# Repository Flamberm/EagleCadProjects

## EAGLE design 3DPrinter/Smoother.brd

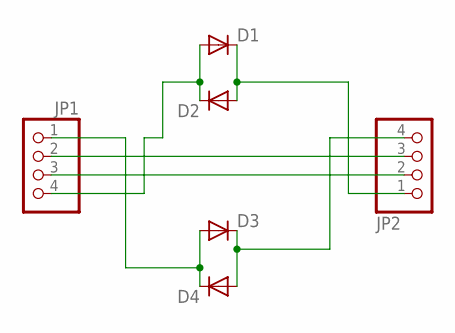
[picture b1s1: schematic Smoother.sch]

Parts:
D1, D2, D3, D4: DIODE_ES1J; DO214AC
JP1, JP2: PINHD-1X4/90; 1X04/90

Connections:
unnamed: D3.A, D4.C, JP1.1
unnamed: JP1.2, JP2.3
unnamed: JP1.3, JP2.2
unnamed: D1.C, D2.A, JP2.1
unnamed: D1.A, D2.C, JP1.4
unnamed: D3.C, D4.A, JP2.4

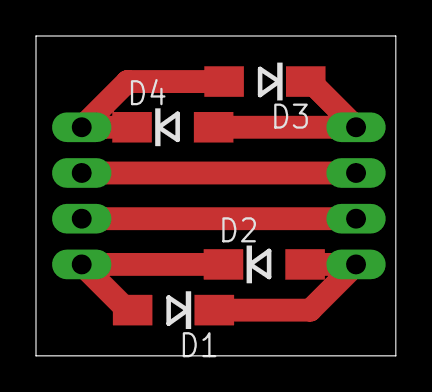
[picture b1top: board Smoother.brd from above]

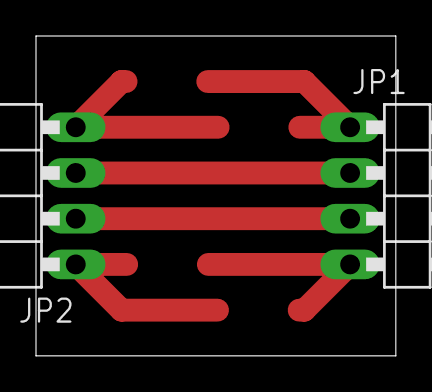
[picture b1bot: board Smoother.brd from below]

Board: 2 copper layers, 20.0 x 17.8 mm, 6 parts (2 on the bottom side), 6 nets.

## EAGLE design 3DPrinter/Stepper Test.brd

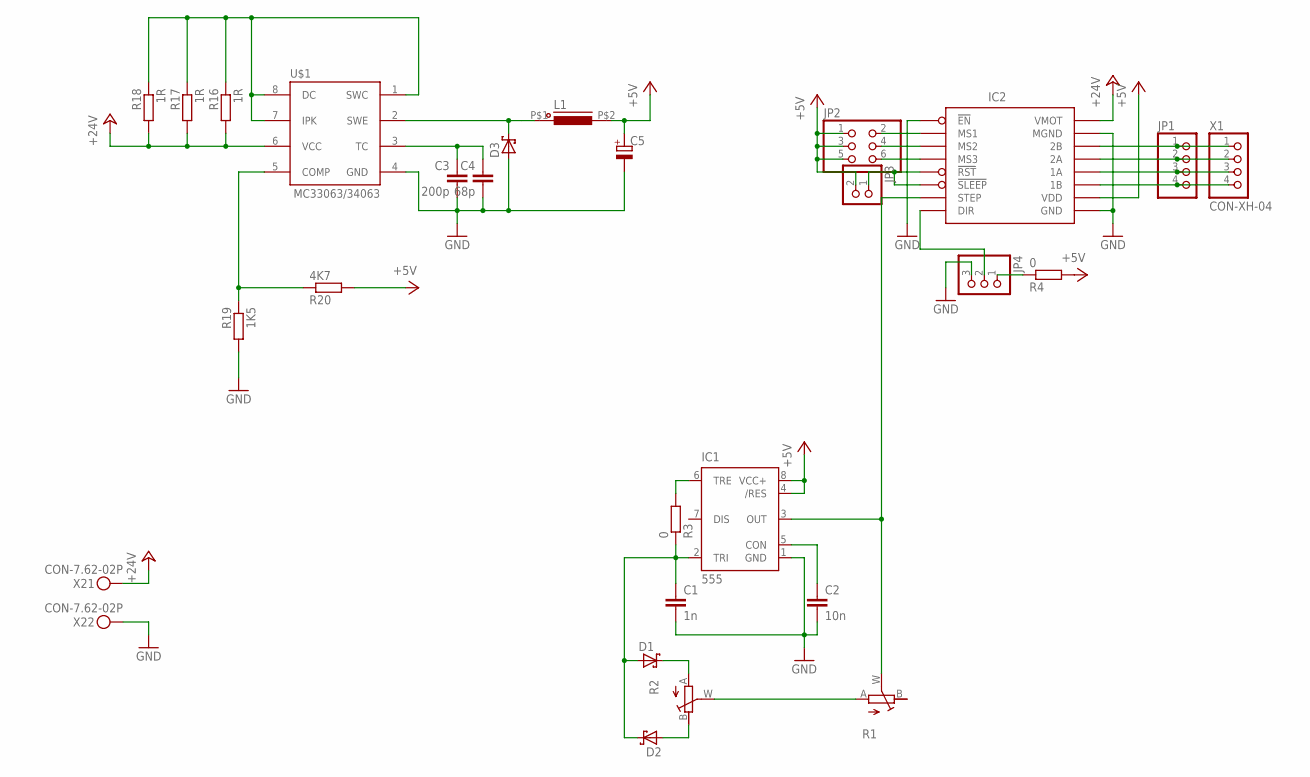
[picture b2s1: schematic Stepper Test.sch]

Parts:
C1: 1n; C0805
C2: 10n; C0805
C3: 200p; C0805
C4: 68p; C0805
C5: CAP-POL_E3.5-8; E3,5-8
D1, D2: DIODE-SH_SOD523; SOD523
D3: DIODE-SH_SMA; DO214AC
IC1: 555; SO08
IC2: STEP-DRV; DRV-BRK
JP1: PINHD-1X4; 1X04
JP2: PINHD-2X3; 2X03
JP3: PINHD-1X2; 1X02
JP4: PINHD-1X3; 1X03
L1: INDUCTORCW68; CW68
R1, R2: R_POTTURN-X; RJ9W
R3, R4: 0; R0805
R16, R17, R18: 1R; R0805
R19: 1K5; R0805
R20: 4K7; R0805
U$1: MC33063/MC34063P; DIL08
X1: CON-XH-04; XH-04
X2: CON-7.62-02P; KF25C-7.62-02P-13

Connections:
+5V: C5.+, IC1.4 (/RES), IC1.8 (VCC+), IC2.P$10 (VDD), JP2.1, JP2.3, JP2.5, JP3.2, L1.P$2 (2), R4.2, R20.2
+24V: IC2.P$16 (VMOT), R16.2, R17.2, R18.2, U$1.6 (VCC), X2.P$1
GND: C1.2, C2.2, C3.2, C4.2, C5.-, D3.A, IC1.1 (GND), IC2.P$1 (!EN), IC2.P$9 (GND), IC2.P$15 (MGND), JP4.3, R19.2, U$1.4 (GND), X2.P$2
unnamed: C1.1, D1.A, D2.C, IC1.2 (TRI), R3.1
unnamed: IC2.P$14 (2B), JP1.1, X1.1
unnamed: C2.1, IC1.5 (CON)
unnamed: IC2.P$13 (2A), JP1.2, X1.2
unnamed: IC2.P$12 (1A), JP1.3, X1.3
unnamed: IC2.P$11 (1B), JP1.4, X1.4
unnamed: IC2.P$2 (MS1), JP2.2
unnamed: IC2.P$3 (MS2), JP2.4
unnamed: R1.A, R2.W (S)
unnamed: IC1.3 (OUT), IC2.P$7 (STEP), R1.W (S)
unnamed: D1.C, R2.A
unnamed: D2.A, R2.B (E)
unnamed: IC2.P$4 (MS3), JP2.6
unnamed: IC2.P$5 (!RST), IC2.P$6 (!SLEEP), JP3.1
unnamed: IC1.6 (TRE), R3.2
unnamed: IC2.P$8 (DIR), JP4.2
unnamed: JP4.1, R4.1
unnamed: C3.1, C4.1, U$1.3 (TC)
unnamed: R16.1, R17.1, R18.1, U$1.1 (SWC), U$1.7 (IPK), U$1.8 (DC)
unnamed: D3.C, L1.P$1 (1), U$1.2 (SWE)
unnamed: R19.1, R20.1, U$1.5 (COMP)

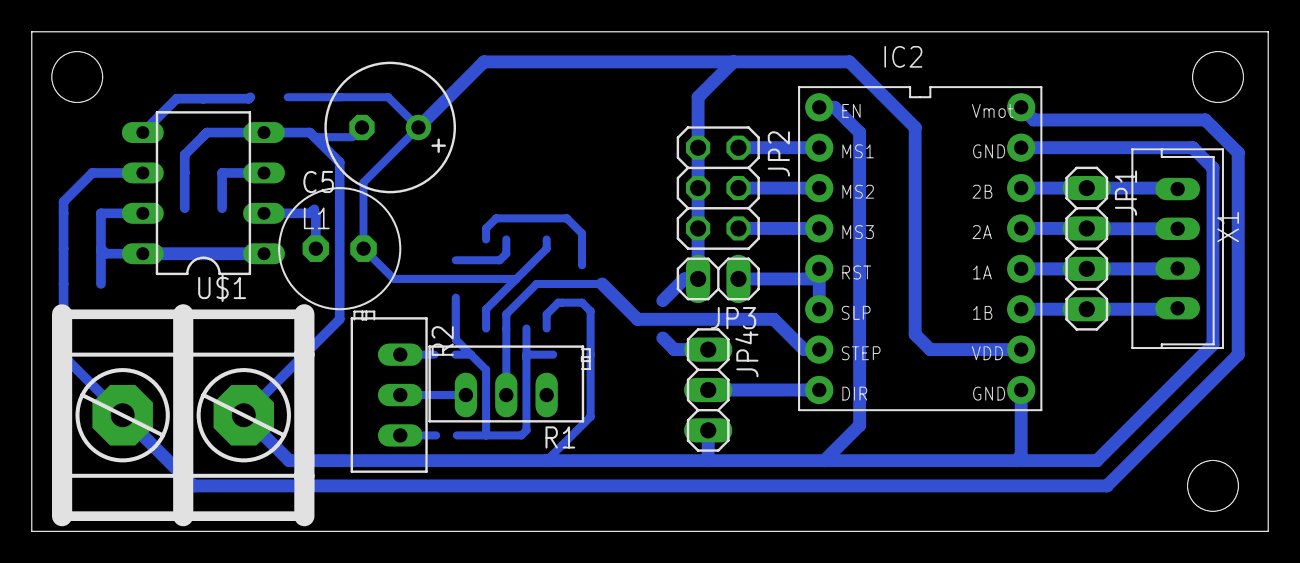
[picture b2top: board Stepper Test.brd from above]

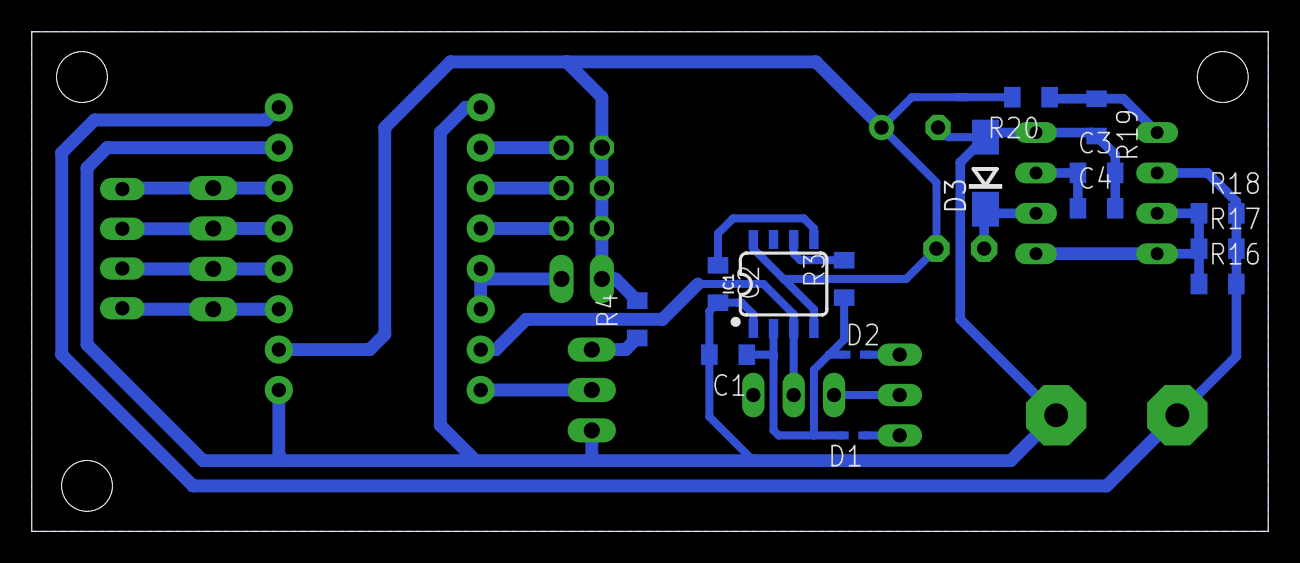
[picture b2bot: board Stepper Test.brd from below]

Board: 2 copper layers, 77.8 x 31.4 mm, 27 parts (15 on the bottom side), 24 nets.

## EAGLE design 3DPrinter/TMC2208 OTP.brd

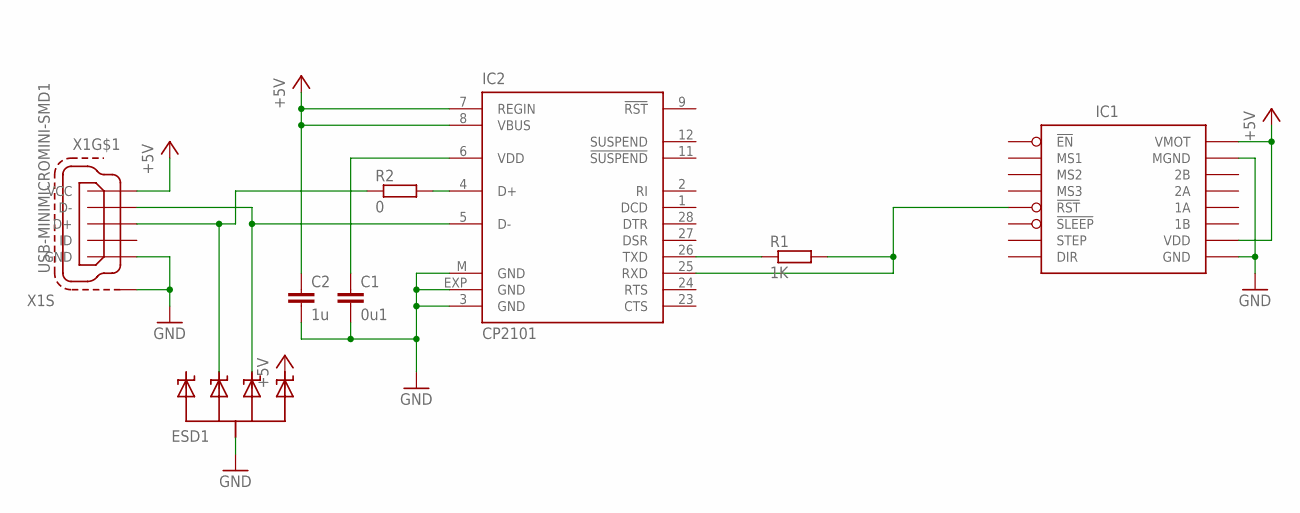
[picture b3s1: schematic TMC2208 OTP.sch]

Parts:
C1: 0u1; C0805
C2: 1u; C0805
ESD1: ESDAXXSC5; SOT23-5L
IC1: STEP-DRV; DRV-BRK
IC2: CP2101; MLP28
R1: 1K; R0805
R2: 0; R0805
X1: USB-MINIMICROMINI-SMD1; 32005-201

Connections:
+5V: C2.1, ESD1.5 (C4), IC1.P$10 (VDD), IC1.P$16 (VMOT), IC2.7 (REGIN), IC2.8 (VBUS), X1.1 (VCC)
GND: C1.2, C2.2, ESD1.2 (A), IC1.P$9 (GND), IC1.P$15 (MGND), IC2.3 (GND), IC2.EXP (GND), IC2.M (GND), X1.5 (GND), X1.M1 (S1), X1.M2 (S1), X1.M3 (S1), X1.M4 (S1)
unnamed: C1.1, IC2.6 (VDD)
unnamed: IC2.26 (TXD), R1.1
unnamed: IC1.P$5 (!RST), IC2.25 (RXD), R1.2
unnamed: IC2.4 (D+), R2.2
unnamed: ESD1.4 (C3), IC2.5 (D-), X1.2 (D-)
unnamed: ESD1.3 (C2), R2.1, X1.3 (D+)

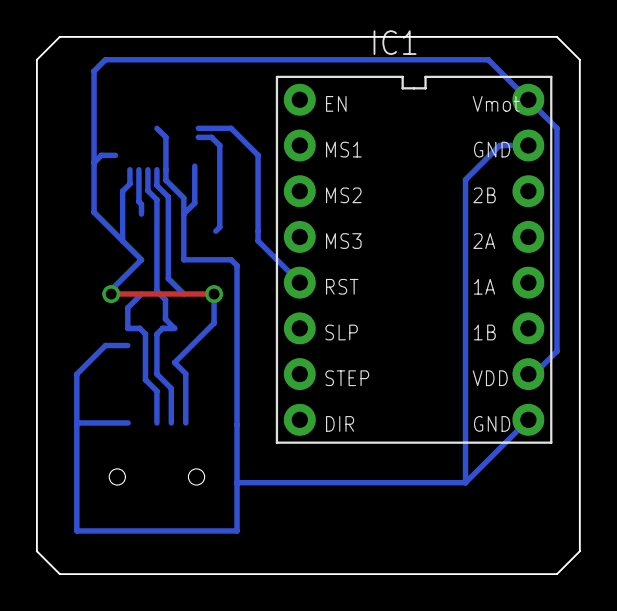
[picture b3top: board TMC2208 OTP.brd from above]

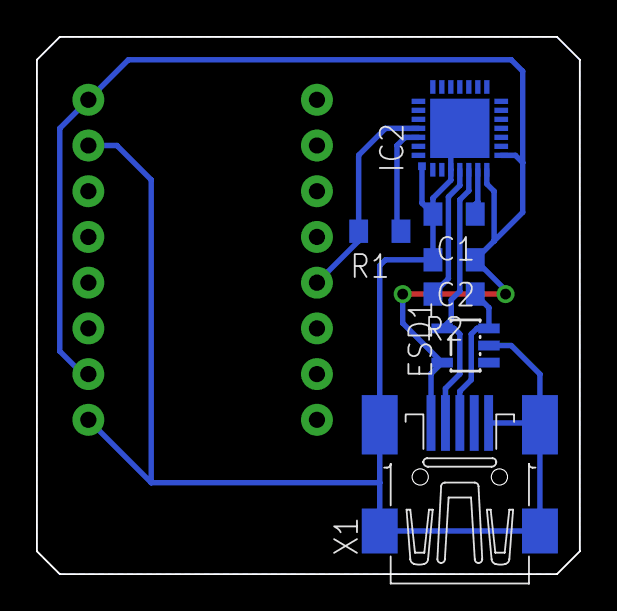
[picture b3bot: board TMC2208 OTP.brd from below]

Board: 2 copper layers, 30.2 x 29.8 mm, 8 parts (7 on the bottom side), 8 nets.

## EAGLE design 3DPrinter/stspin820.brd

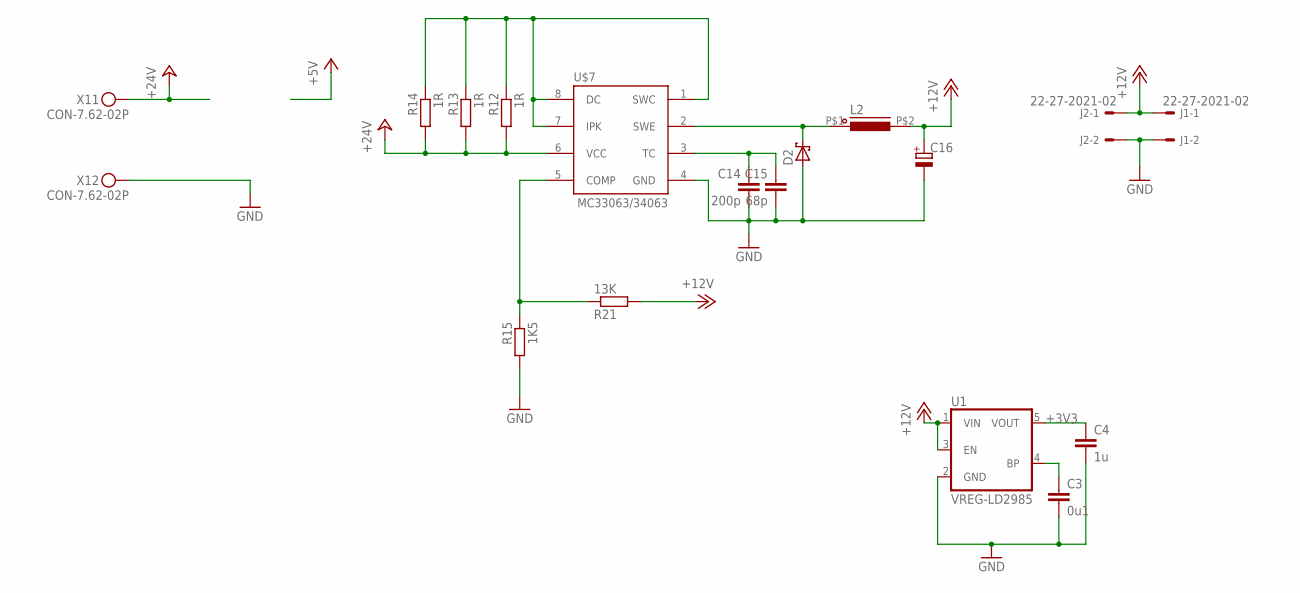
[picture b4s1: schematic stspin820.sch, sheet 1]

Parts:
C3: 0u1; CAP0805
C4: 1u; CAP0805
C14: 200p; CAP0805
C15: 68p; CAP0805
C16: CAP-POL_E3.5-8; E3,5-8
D2: DIODE-SH_SMA; DO214AC
J1, J2: 22-27-2021-02; 6410-02
L2: INDUCTORCW68; CW68
R12, R13, R14: 1R; RESC2012X50
R15: 1K5; RESC2012X50
R21: 13K; RESC2012X50
U1: VREG-LD2985; SOT95P280X145-5
U$7: MC33063/MC34063P; DIL08
X1: CON-7.62-02P; KF25C-7.62-02P-13

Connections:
+3V3: C4.1, U1.5 (VOUT); also elsewhere on the board
+12V: C16.+, J1.1, J2.1, L2.P$2 (2), R21.2, U1.1 (VIN), U1.3 (EN)
+24V: R12.2, R13.2, R14.2, U$7.6 (VCC), X1.P$1; also elsewhere on the board
GND: C3.2, C4.2, C14.2, C15.2, C16.-, D2.A, J1.2, J2.2, R15.2, U1.2 (GND), U$7.4 (GND), X1.P$2; also elsewhere on the board
unnamed: C14.1, C15.1, U$7.3 (TC)
unnamed: R12.1, R13.1, R14.1, U$7.1 (SWC), U$7.7 (IPK), U$7.8 (DC)
unnamed: D2.C, L2.P$1 (1), U$7.2 (SWE)
unnamed: R15.1, R21.1, U$7.5 (COMP)
unnamed: C3.1, U1.4 (BP)

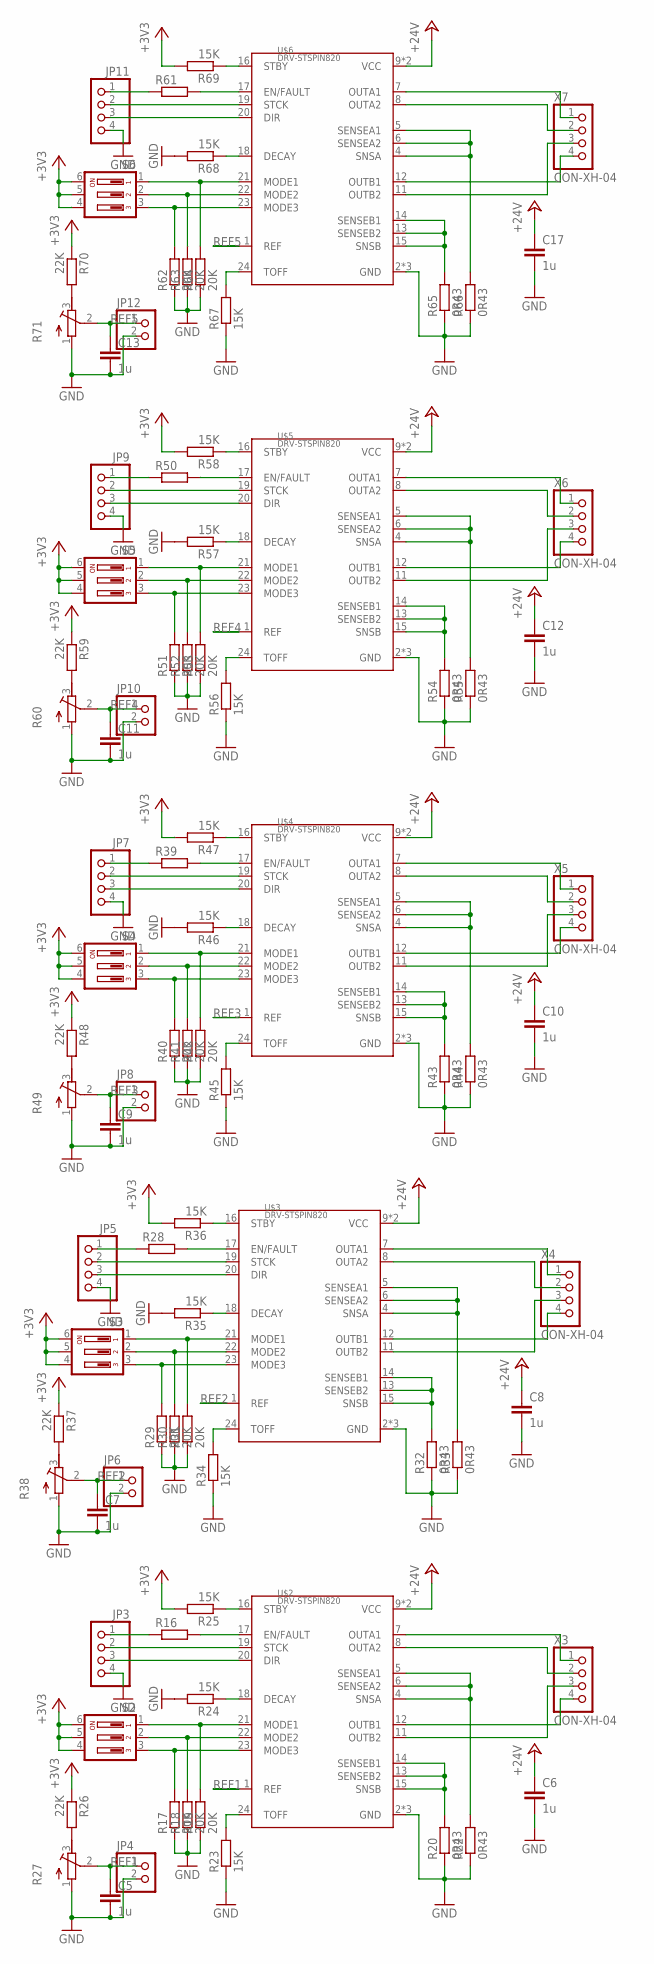
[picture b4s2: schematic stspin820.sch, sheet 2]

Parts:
C5, C6, C7, C8, C9, C10, C11, C12, C13, C17: 1u; CAP0805
JP3, JP5, JP7, JP9, JP11: PINHD-1X4; 1X04
JP4, JP6, JP8, JP10, JP12: PINHD-1X2; 1X02
R16, R28, R39, R50, R61: R_R0805; RESC2012X50
R17, R18, R19, R29, R30, R31, R40, R41, R42, R51, R52, R53, R62, R63, R64: 20K; RESC2012X50
R20, R22, R32, R33, R43, R44, R54, R55, R65, R66: 0R43; RESC3216X60
R23, R24, R25, R34, R35, R36, R45, R46, R47, R56, R57, R58, R67, R68, R69: 15K; RESC2012X50
R26, R37, R48, R59, R70: 22K; RESC2012X50
R27, R38, R49, R60, R71: R_POT3296X; POT-3296X
S2, S3, S4, S5, S6: SW-DIP03S; DIP03YL
U$2, U$3, U$4, U$5, U$6: DRV-STSPIN820; QFN24
X3, X4, X5, X6, X7: CON-XH-04; XH-04

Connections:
+3V3: R25.2, R26.1, R36.2, R37.1, R47.2, R48.1, R58.2, R59.1, R69.2, R70.1, S2.4, S2.5, S2.6, S3.4, S3.5, S3.6, S4.4, S4.5, S4.6, S5.4, S5.5, S5.6, S6.4, S6.5, S6.6; also elsewhere on the board
+24V: C6.1, C8.1, C10.1, C12.1, C17.1, U$2.9 (VCC), U$2.10 (VCC), U$3.9 (VCC), U$3.10 (VCC), U$4.9 (VCC), U$4.10 (VCC), U$5.9 (VCC), U$5.10 (VCC), U$6.9 (VCC), U$6.10 (VCC); also elsewhere on the board
GND: C5.2, C6.2, C7.2, C8.2, C9.2, C10.2, C11.2, C12.2, C13.2, C17.2, JP3.4, JP4.2, JP5.4, JP6.2, JP7.4, JP8.2, JP9.4, JP10.2, JP11.4, JP12.2, R17.1, R18.1, R19.1, R20.1, R22.1, R23.1, R24.2, R27.1 (A), R29.1, R30.1, R31.1, R32.1, R33.1, R34.1, R35.2, R38.1 (A), R40.1, R41.1, R42.1, R43.1, R44.1, R45.1, R46.2, R49.1 (A), R51.1, R52.1, R53.1, R54.1, R55.1, R56.1, R57.2, R60.1 (A), R62.1, R63.1, R64.1, R65.1, R66.1, R67.1, R68.2, R71.1 (A), U$2.2 (GND), U$2.3 (GND), U$2.PAD (GND), U$3.2 (GND), U$3.3 (GND), U$3.PAD (GND), U$4.2 (GND), U$4.3 (GND), U$4.PAD (GND), U$5.2 (GND), U$5.3 (GND), U$5.PAD (GND), U$6.2 (GND), U$6.3 (GND), U$6.PAD (GND); also elsewhere on the board
unnamed: JP3.2, U$2.19 (STCK)
unnamed: JP3.3, U$2.20 (DIR)
unnamed: JP3.1, R16.1
unnamed: R16.2, U$2.17 (EN/FAULT)
unnamed: R19.2, S2.1, U$2.21 (MODE1)
unnamed: R18.2, S2.2, U$2.22 (MODE2)
unnamed: R17.2, S2.3, U$2.23 (MODE3)
unnamed: R20.2, U$2.13 (SENSEB2), U$2.14 (SENSEB1), U$2.15 (SNSB)
unnamed: R22.2, U$2.4 (SNSA), U$2.5 (SENSEA1), U$2.6 (SENSEA2)
unnamed: U$2.7 (OUTA1), X3.1
unnamed: U$2.8 (OUTA2), X3.2
unnamed: R23.2, U$2.24 (TOFF)
unnamed: R25.1, U$2.16 (STBY)
unnamed: R24.1, U$2.18 (DECAY)
unnamed: U$2.11 (OUTB2), X3.3
unnamed: U$2.12 (OUTB1), X3.4
unnamed: R26.2, R27.3 (E)
unnamed: JP5.2, U$3.19 (STCK)
unnamed: JP5.3, U$3.20 (DIR)
unnamed: JP5.1, R28.1
unnamed: R28.2, U$3.17 (EN/FAULT)
unnamed: R31.2, S3.1, U$3.21 (MODE1)
unnamed: R30.2, S3.2, U$3.22 (MODE2)
unnamed: R29.2, S3.3, U$3.23 (MODE3)
unnamed: R32.2, U$3.13 (SENSEB2), U$3.14 (SENSEB1), U$3.15 (SNSB)
unnamed: R33.2, U$3.4 (SNSA), U$3.5 (SENSEA1), U$3.6 (SENSEA2)
unnamed: U$3.7 (OUTA1), X4.1
unnamed: U$3.8 (OUTA2), X4.2
unnamed: R34.2, U$3.24 (TOFF)
unnamed: R36.1, U$3.16 (STBY)
unnamed: R35.1, U$3.18 (DECAY)
unnamed: U$3.11 (OUTB2), X4.3
unnamed: U$3.12 (OUTB1), X4.4
unnamed: R37.2, R38.3 (E)
unnamed: JP7.2, U$4.19 (STCK)
unnamed: JP7.3, U$4.20 (DIR)
unnamed: JP7.1, R39.1
unnamed: R39.2, U$4.17 (EN/FAULT)
unnamed: R42.2, S4.1, U$4.21 (MODE1)
unnamed: R41.2, S4.2, U$4.22 (MODE2)
unnamed: R40.2, S4.3, U$4.23 (MODE3)
unnamed: R43.2, U$4.13 (SENSEB2), U$4.14 (SENSEB1), U$4.15 (SNSB)
unnamed: R44.2, U$4.4 (SNSA), U$4.5 (SENSEA1), U$4.6 (SENSEA2)
unnamed: U$4.7 (OUTA1), X5.1
unnamed: U$4.8 (OUTA2), X5.2
unnamed: R45.2, U$4.24 (TOFF)
unnamed: R47.1, U$4.16 (STBY)
unnamed: R46.1, U$4.18 (DECAY)
unnamed: U$4.11 (OUTB2), X5.3
unnamed: U$4.12 (OUTB1), X5.4
unnamed: R48.2, R49.3 (E)
unnamed: JP9.2, U$5.19 (STCK)
unnamed: JP9.3, U$5.20 (DIR)
unnamed: JP9.1, R50.1
unnamed: R50.2, U$5.17 (EN/FAULT)
unnamed: R53.2, S5.1, U$5.21 (MODE1)
unnamed: R52.2, S5.2, U$5.22 (MODE2)
unnamed: R51.2, S5.3, U$5.23 (MODE3)
unnamed: R54.2, U$5.13 (SENSEB2), U$5.14 (SENSEB1), U$5.15 (SNSB)
unnamed: R55.2, U$5.4 (SNSA), U$5.5 (SENSEA1), U$5.6 (SENSEA2)
unnamed: U$5.7 (OUTA1), X6.1
unnamed: U$5.8 (OUTA2), X6.2
unnamed: R56.2, U$5.24 (TOFF)
unnamed: R58.1, U$5.16 (STBY)
unnamed: R57.1, U$5.18 (DECAY)
unnamed: U$5.11 (OUTB2), X6.3
unnamed: U$5.12 (OUTB1), X6.4
unnamed: R59.2, R60.3 (E)
unnamed: JP11.2, U$6.19 (STCK)
unnamed: JP11.3, U$6.20 (DIR)
unnamed: JP11.1, R61.1
unnamed: R61.2, U$6.17 (EN/FAULT)
unnamed: R64.2, S6.1, U$6.21 (MODE1)
unnamed: R63.2, S6.2, U$6.22 (MODE2)
unnamed: R62.2, S6.3, U$6.23 (MODE3)
unnamed: R65.2, U$6.13 (SENSEB2), U$6.14 (SENSEB1), U$6.15 (SNSB)
unnamed: R66.2, U$6.4 (SNSA), U$6.5 (SENSEA1), U$6.6 (SENSEA2)
unnamed: U$6.7 (OUTA1), X7.1
unnamed: U$6.8 (OUTA2), X7.2
unnamed: R67.2, U$6.24 (TOFF)
unnamed: R69.1, U$6.16 (STBY)
unnamed: R68.1, U$6.18 (DECAY)
unnamed: U$6.11 (OUTB2), X7.3
unnamed: U$6.12 (OUTB1), X7.4
unnamed: R70.2, R71.3 (E)
REF1: C5.1, JP4.1, R27.2 (S), U$2.1 (REF)
REF2: C7.1, JP6.1, R38.2 (S), U$3.1 (REF)
REF3: C9.1, JP8.1, R49.2 (S), U$4.1 (REF)
REF4: C11.1, JP10.1, R60.2 (S), U$5.1 (REF)
REF5: C13.1, JP12.1, R71.2 (S), U$6.1 (REF)

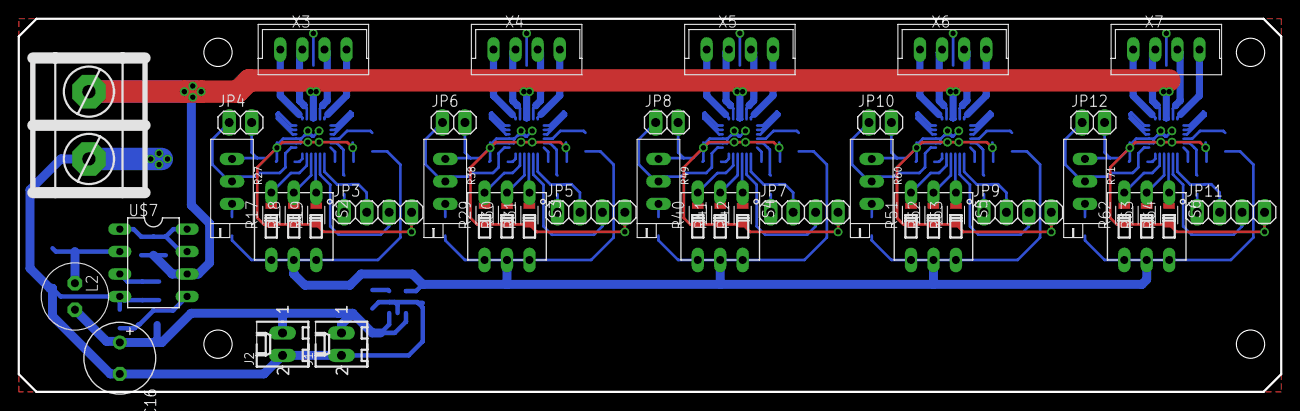
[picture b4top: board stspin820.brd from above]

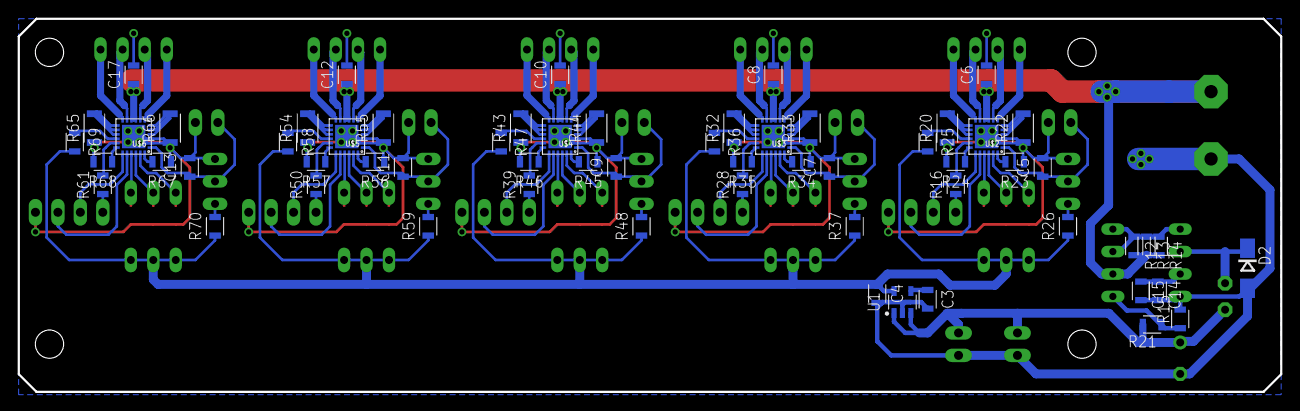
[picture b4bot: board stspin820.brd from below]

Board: 2 copper layers, 142.9 x 42.2 mm, 107 parts (61 on the bottom side), 99 nets.

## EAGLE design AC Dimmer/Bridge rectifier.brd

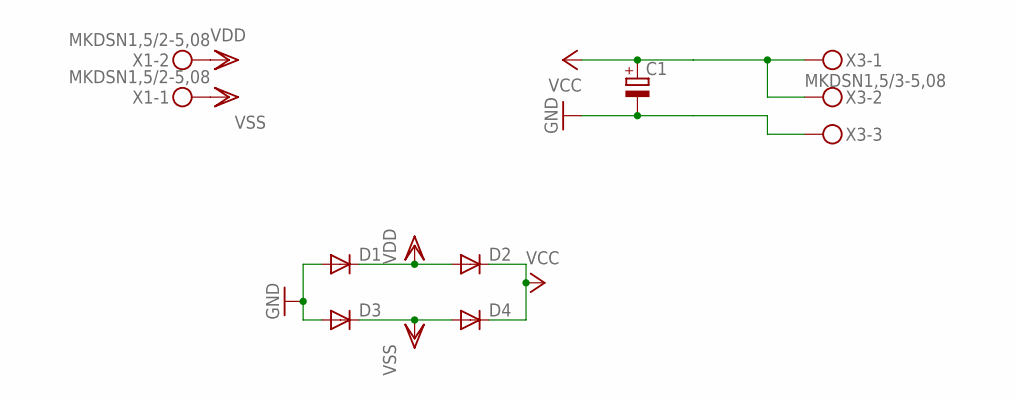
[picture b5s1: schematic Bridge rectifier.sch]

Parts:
C1: CPOL-EUE2.5-7; E2,5-7
D1, D2, D3, D4: DIODE-DO-214AC; DO-214AC
X1: MKDSN1,5/2-5,08
X3: MKDSN1,5/3-5,08

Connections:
GND: C1.-, D1.A, D3.A, X3.3
VCC: C1.+, D2.C, D4.C, X3.1, X3.2
VDD: D1.C, D2.A, X1.2
VSS: D3.C, D4.A, X1.1

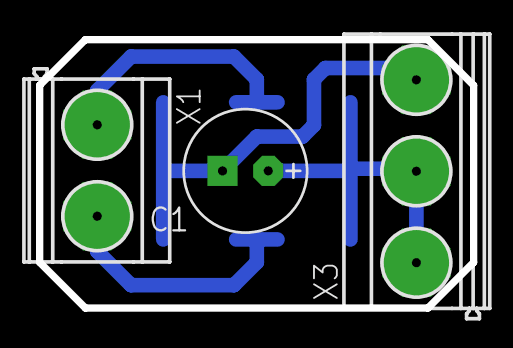
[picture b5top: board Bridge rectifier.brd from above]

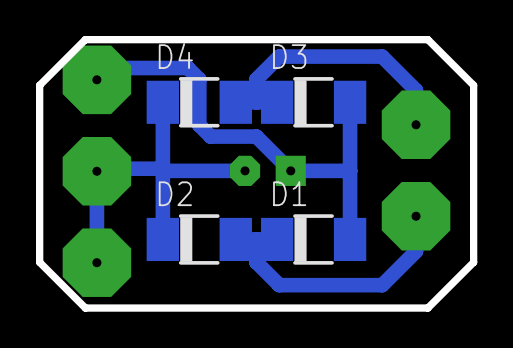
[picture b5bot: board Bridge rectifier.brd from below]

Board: 2 copper layers, 24.1 x 14.9 mm, 7 parts (4 on the bottom side), 4 nets.

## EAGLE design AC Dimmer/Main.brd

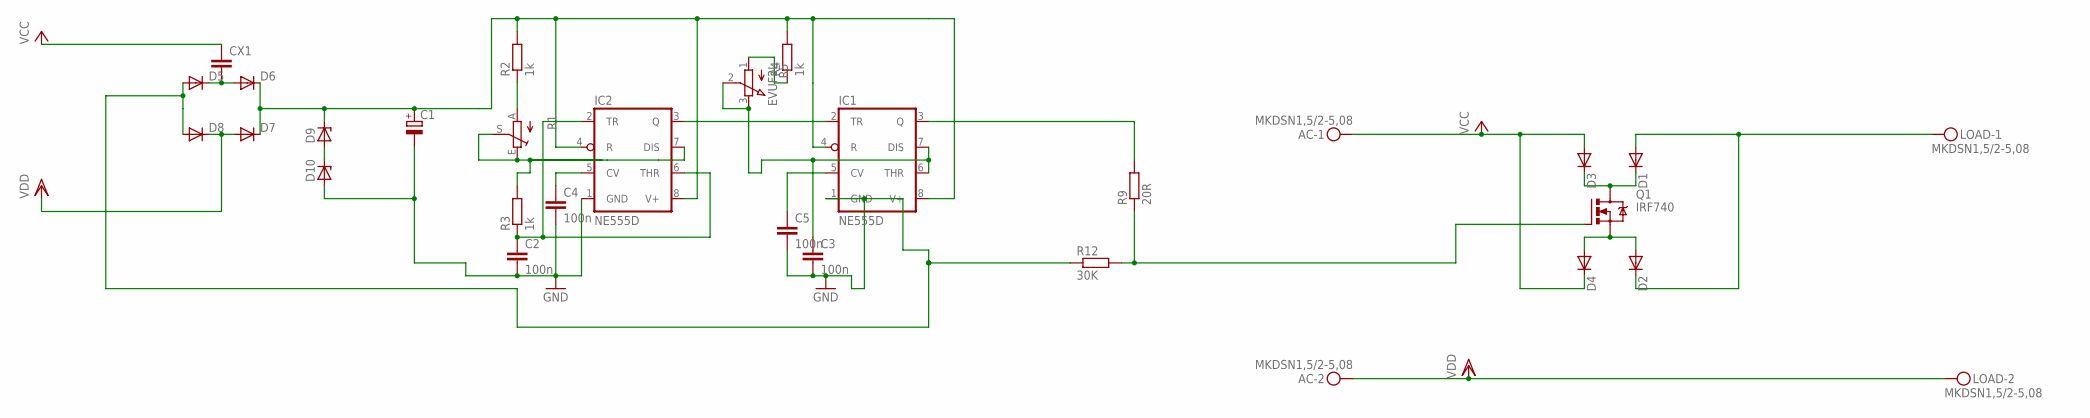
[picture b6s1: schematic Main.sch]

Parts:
AC: MKDSN1,5/2-5,08
C1: CPOL-EUE2.5-7; E2,5-7
C2, C3, C4, C5: 100n; C0805
CX1: CXXC15B8; XC15B8
D1, D2, D3, D4: DIODE-DO220S; DO220S
D5, D6, D7, D8: DIODE-DO-214AC; DO-214AC
D9, D10: ZENER-DIODESOD80C; SOD80C
IC1, IC2: NE555D; SO08
LOAD: MKDSN1,5/2-5,08
Q1: IRF740; TO220BV
R1: TRIM_EU-S75H; S75H
R2, R3, R4: 1k; R1206
R5: EVUF2L; EVUFXL
R9: 20R; R1206
R12: 30K; R0805

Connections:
GND: C1.-, C2.2, C3.2, C4.2, C5.2, D5.A, D8.A, D10.A, IC1.1 (GND), IC2.1 (GND), R12.1
unnamed: D2.A, D4.A, Q1.S
unnamed: D1.C, D3.C, Q1.D
unnamed: IC1.3 (Q), R9.2
unnamed: D1.A, D2.C, LOAD.1
unnamed: CX1.2, D5.C, D6.A
unnamed: C1.+, D6.C, D7.C, D9.C, IC1.4 (R), IC1.8 (V+), IC2.4 (R), IC2.8 (V+), R2.2, R4.2
unnamed: D9.A, D10.C
unnamed: R1.A, R2.1
unnamed: IC2.7 (DIS), R1.E, R1.S, R3.2
unnamed: C2.1, IC2.2 (TR), IC2.6 (THR), R3.1
unnamed: IC1.2 (TR), IC2.3 (Q)
unnamed: C4.1, IC2.5 (CV)
unnamed: C5.1, IC1.5 (CV)
unnamed: Q1.G, R9.1, R12.2
unnamed: R4.1, R5.1 (A)
unnamed: C3.1, IC1.6 (THR), IC1.7 (DIS), R5.2 (S), R5.3 (E)
VCC: AC.1, CX1.1, D3.A, D4.C
VDD: AC.2, D7.A, D8.C, LOAD.2

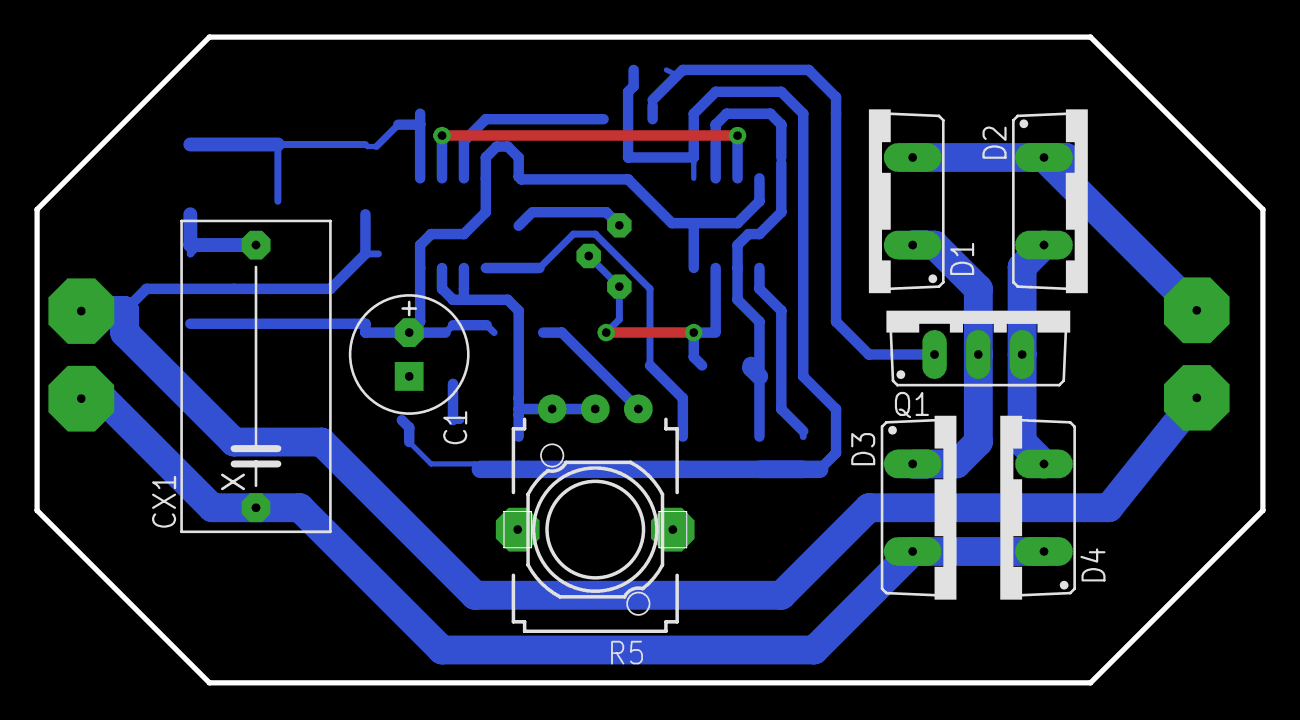
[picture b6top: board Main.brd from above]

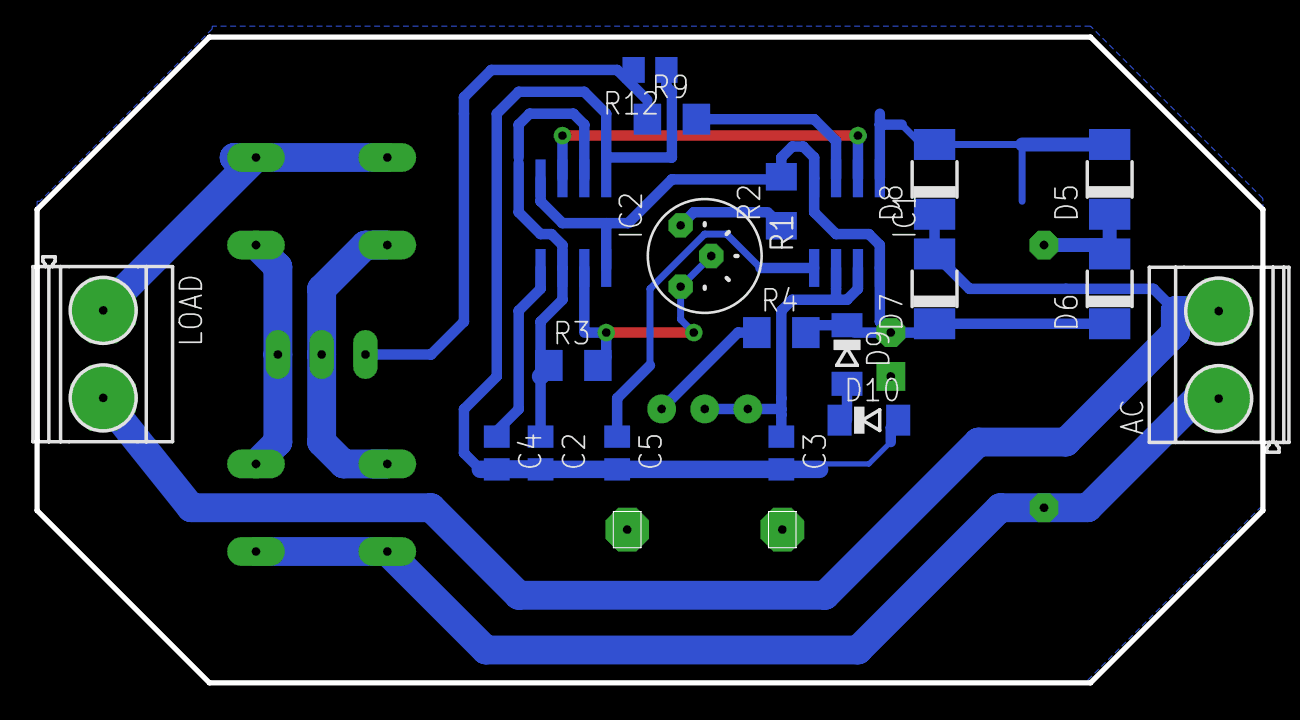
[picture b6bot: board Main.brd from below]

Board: 2 copper layers, 71.1 x 37.5 mm, 28 parts (20 on the bottom side), 19 nets.

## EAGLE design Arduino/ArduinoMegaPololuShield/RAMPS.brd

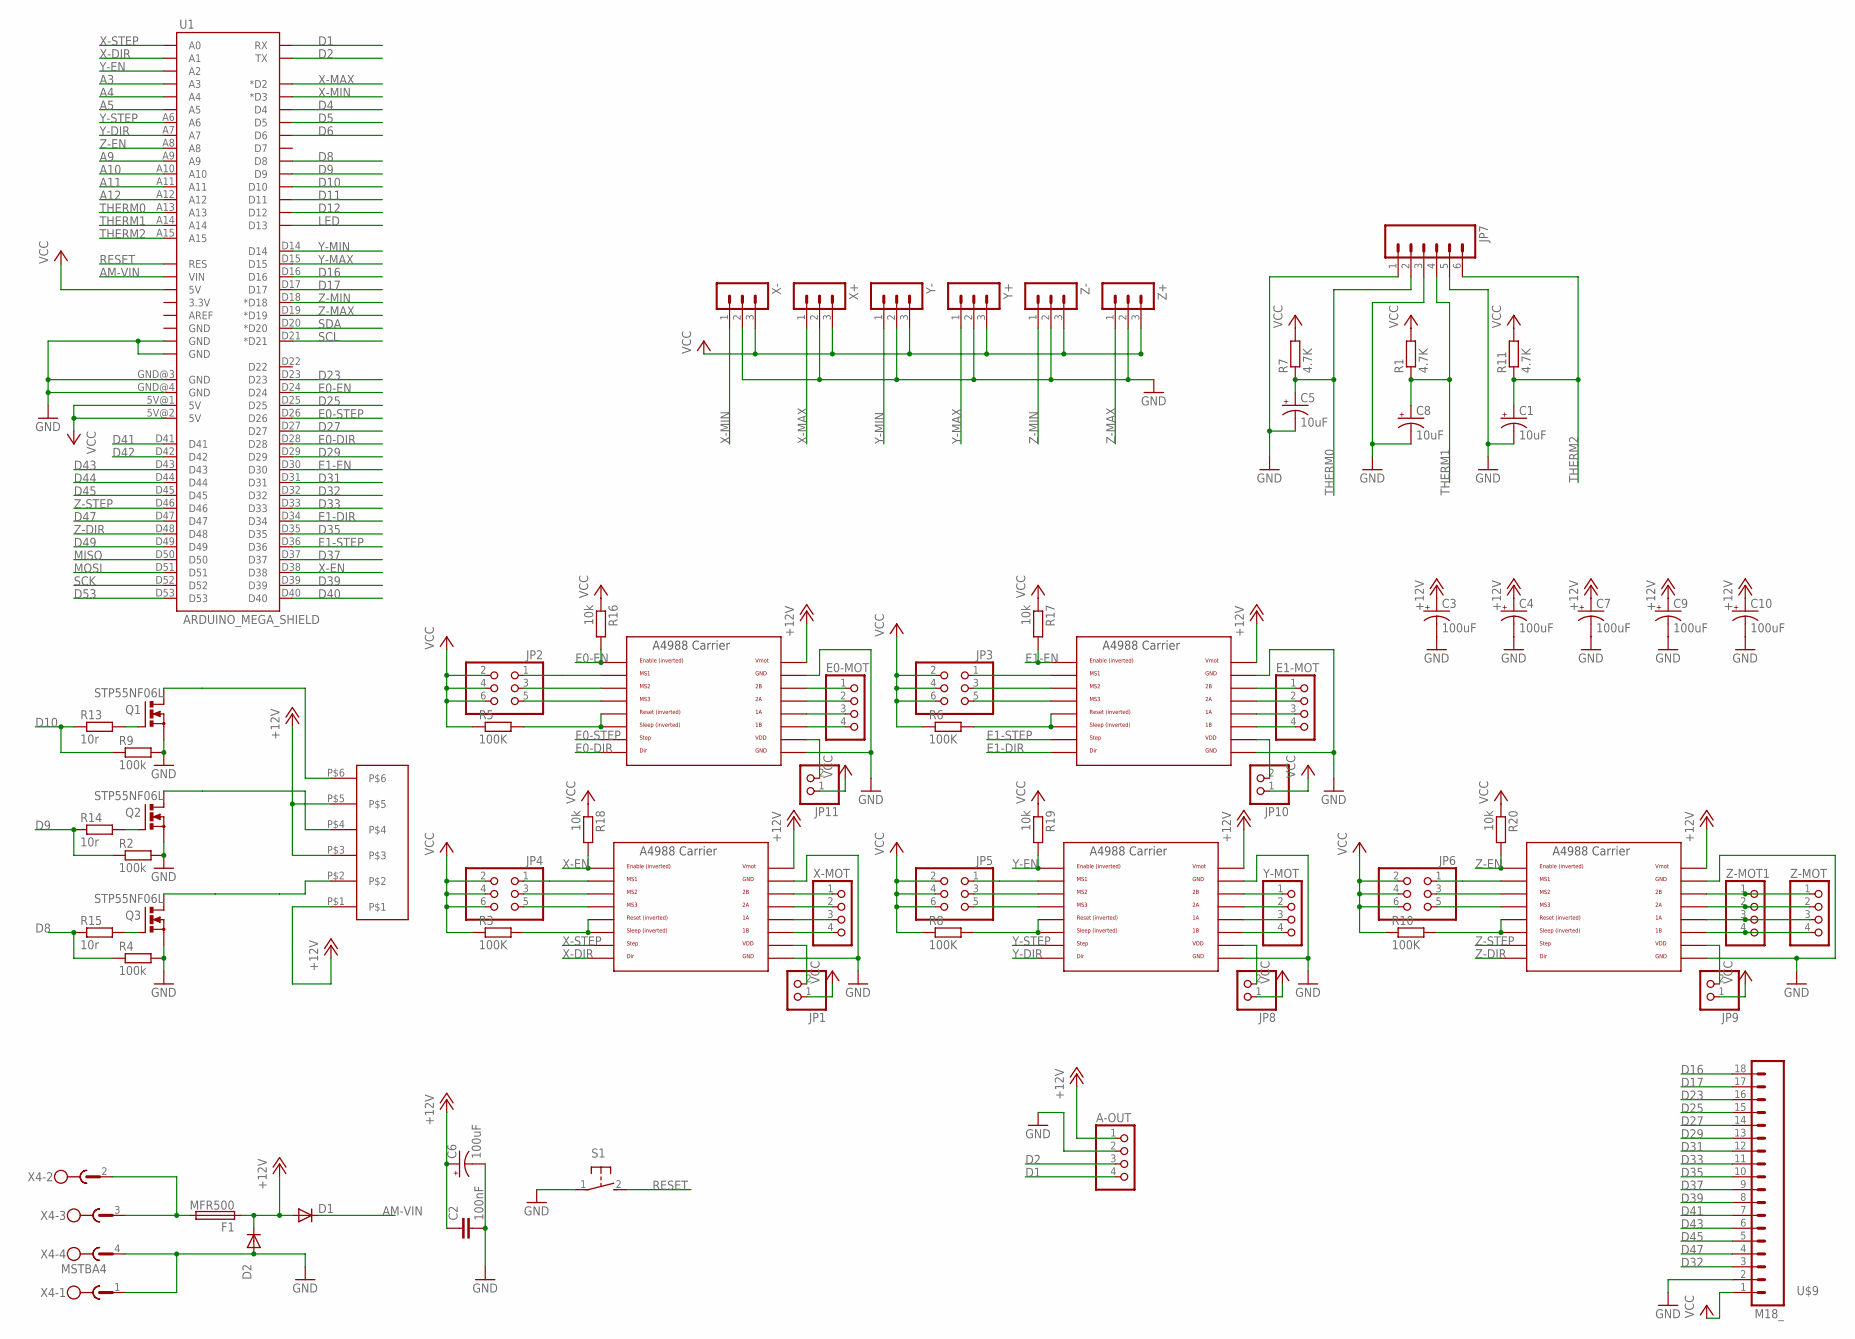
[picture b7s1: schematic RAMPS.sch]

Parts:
A-OUT: PINHD-1X4; 1X04
C1, C5, C8: 10uF; 153CLV-0405
C2: 100nF; C0805
C3, C4, C6, C7, C9, C10: 100uF; 153CLV-0605
D1, D2: DIODE-DO-214AC; DO-214AC
E0-MOT, E1-MOT: PINHD-1X4; 1X04
F1: MFR500
JP1, JP8, JP9, JP10, JP11: PINHD-1X2; 1X02
JP2, JP3, JP4, JP5, JP6: PINHD-2X3; 2X03
JP7: M06SIP; 1X06
Q1, Q2, Q3: STP55NF06L; TO220BV
R1, R7, R11: 4.7K; R1206
R2, R4, R9: 100k; R0805
R3, R5, R6, R8, R10: 100K; R0805
R13, R14, R15: 10r; R0805
R16, R17, R18, R19, R20: 10k; R0805
S1: 31-XX; B3F-31XX
U1: ARDUINO_MEGA_SHIELD
U$2: 282837-6
U$4, U$5, U$6, U$7, U$8: A4988BREAKOUT
U$9: M18_; 1X18
X4: MSTBA4
X+: 3PIN-HEADER
X-: 3PIN-HEADER
X-MOT: PINHD-1X4; 1X04
Y+: 3PIN-HEADER
Y-: 3PIN-HEADER
Y-MOT: PINHD-1X4; 1X04
Z+: 3PIN-HEADER
Z-: 3PIN-HEADER
Z-MOT, Z-MOT1: PINHD-1X4; 1X04

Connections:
+12V: A-OUT.1, C2.1, C3.+, C4.+, C6.+, C7.+, C9.+, C10.+, D1.A, D2.C, F1.1, U$2.P$1, U$2.P$3, U$2.P$5, U$4.VMOT, U$5.VMOT, U$6.VMOT, U$7.VMOT, U$8.VMOT
A3: U1.A3
A4: U1.A4
A5: U1.A5
A9: U1.A9
A10: U1.A10
A11: U1.A11
A12: U1.A12
AM-VIN: D1.C, U1.VIN
D1: A-OUT.4, U1.RX
D2: A-OUT.3, U1.TX
D4: U1.D4
D5: U1.D5
D6: U1.D6
D8: R4.1, R15.1, U1.D8
D9: R2.1, R14.1, U1.D9
D10: R9.1, R13.1, U1.D10
D11: U1.D11
D12: U1.D12
D16: U1.D16, U$9.18
D17: U1.D17, U$9.17
D23: U1.D23, U$9.16
D25: U1.D25, U$9.15
D27: U1.D27, U$9.14
D29: U1.D29, U$9.13
D31: U1.D31, U$9.12
D32: U1.D32, U$9.3
D33: U1.D33, U$9.11
D35: U1.D35, U$9.10
D37: U1.D37, U$9.9
D39: U1.D39, U$9.8
D40: U1.D40
D41: U1.D41, U$9.7
D42: U1.D42
D43: U1.D43, U$9.6
D44: U1.D44
D45: U1.D45, U$9.5
D47: U1.D47, U$9.4
D49: U1.D49
D53: U1.D53
E0-DIR: U1.D28, U$4.DIR
E0-EN: R16.2, U1.D24, U$4.EN
E0-STEP: U1.D26, U$4.STEP
E1-DIR: U1.D34, U$5.DIR
E1-EN: R17.2, U1.D30, U$5.EN
E1-STEP: U1.D36, U$5.STEP
GND: A-OUT.2, C1.-, C2.2, C3.-, C4.-, C5.-, C6.-, C7.-, C8.-, C9.-, C10.-, D2.A, JP7.1, JP7.3, JP7.5, Q1.S, Q2.S, Q3.S, R2.2, R4.2, R9.2, S1.1, U1.GND@0 (GND), U1.GND@1 (GND), U1.GND@3 (GND), U1.GND@4 (GND), U$4.GND, U$4.GND@0 (GND), U$5.GND, U$5.GND@0 (GND), U$6.GND, U$6.GND@0 (GND), U$7.GND, U$7.GND@0 (GND), U$8.GND, U$8.GND@0 (GND), U$9.2, X4.1, X4.4, X+.2, X-.2, Y+.2, Y-.2, Z+.2, Z-.2
LED: U1.D13
MISO: U1.D50
MOSI: U1.D51
unnamed: Q2.D, U$2.P$4
unnamed: F1.2, X4.2, X4.3
unnamed: E0-MOT.1, U$4.2B
unnamed: E0-MOT.2, U$4.2A
unnamed: JP2.1, U$4.MS1
unnamed: JP2.5, U$4.MS3
unnamed: Q1.D, U$2.P$6
unnamed: R5.2, U$4.RST, U$4.SLP (SLEEP)
unnamed: JP2.3, U$4.MS2
unnamed: E0-MOT.3, U$4.1A
unnamed: E0-MOT.4, U$4.1B
unnamed: E1-MOT.1, U$5.2B
unnamed: E1-MOT.2, U$5.2A
unnamed: JP4.1, U$6.MS1
unnamed: JP4.3, U$6.MS2
unnamed: E1-MOT.3, U$5.1A
unnamed: JP5.3, U$7.MS2
unnamed: E1-MOT.4, U$5.1B
unnamed: JP4.5, U$6.MS3
unnamed: R3.2, U$6.RST, U$6.SLP (SLEEP)
unnamed: U$6.2B, X-MOT.1
unnamed: U$6.2A, X-MOT.2
unnamed: R8.2, U$7.RST, U$7.SLP (SLEEP)
unnamed: R6.2, U$5.RST, U$5.SLP (SLEEP)
unnamed: JP3.1, U$5.MS1
unnamed: U$6.1A, X-MOT.3
unnamed: U$6.1B, X-MOT.4
unnamed: U$7.2B, Y-MOT.1
unnamed: U$7.2A, Y-MOT.2
unnamed: U$7.1A, Y-MOT.3
unnamed: JP5.5, U$7.MS3
unnamed: JP11.2, U$4.VDD
unnamed: JP5.1, U$7.MS1
unnamed: JP3.5, U$5.MS3
unnamed: JP3.3, U$5.MS2
unnamed: U$7.1B, Y-MOT.4
unnamed: JP6.3, U$8.MS2
unnamed: R10.2, U$8.RST, U$8.SLP (SLEEP)
unnamed: JP6.5, U$8.MS3
unnamed: JP6.1, U$8.MS1
unnamed: U$8.2B, Z-MOT.1, Z-MOT1.1
unnamed: U$8.2A, Z-MOT.2, Z-MOT1.2
unnamed: U$8.1A, Z-MOT.3, Z-MOT1.3
unnamed: U$8.1B, Z-MOT.4, Z-MOT1.4
unnamed: JP1.2, U$6.VDD
unnamed: JP8.2, U$7.VDD
unnamed: Q2.G, R14.2
unnamed: Q1.G, R13.2
unnamed: Q3.G, R15.2
unnamed: JP9.2, U$8.VDD
unnamed: Q3.D, U$2.P$2
unnamed: JP10.2, U$5.VDD
RESET: S1.2 (S), U1.RES
SCK: U1.D52
SCL: U1.D21 (*D21)
SDA: U1.D20 (*D20)
THERM0: C5.+, JP7.2, R7.1, U1.A13
THERM1: C8.+, JP7.4, R1.1, U1.A14
THERM2: C1.+, JP7.6, R11.1, U1.A15
VCC: JP1.1, JP2.2, JP2.4, JP2.6, JP3.2, JP3.4, JP3.6, JP4.2, JP4.4, JP4.6, JP5.2, JP5.4, JP5.6, JP6.2, JP6.4, JP6.6, JP8.1, JP9.1, JP10.1, JP11.1, R1.2, R3.1, R5.1, R6.1, R7.2, R8.1, R10.1, R11.2, R16.1, R17.1, R18.1, R19.1, R20.1, U1.5V@0 (5V), U1.5V@1 (5V), U1.5V@2 (5V), U$9.1, X+.3, X-.3, Y+.3, Y-.3, Z+.3, Z-.3
X-DIR: U1.A1, U$6.DIR
X-EN: R18.2, U1.D38, U$6.EN
X-MAX: U1.D2 (*D2), X+.1
X-MIN: U1.D3 (*D3), X-.1
X-STEP: U1.A0, U$6.STEP
Y-DIR: U1.A7, U$7.DIR
Y-EN: R19.2, U1.A2, U$7.EN
Y-MAX: U1.D15, Y+.1
Y-MIN: U1.D14, Y-.1
Y-STEP: U1.A6, U$7.STEP
Z-DIR: U1.D48, U$8.DIR
Z-EN: R20.2, U1.A8, U$8.EN
Z-MAX: U1.D19 (*D19), Z+.1
Z-MIN: U1.D18 (*D18), Z-.1
Z-STEP: U1.D46, U$8.STEP

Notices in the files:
Arduino/ArduinoMegaPololuShield/RAMPS.brd:
GPL v3
Arduino/ArduinoMegaPololuShield/RAMPS.sch:
Copyright 2011 Johnny Russell
parts and their libraries:
SparkFun-IC-Special-Function: Licensing: Creative Commons ShareAlike 4.0 International - https://creativecommons.org/licenses/by-sa/4.0
